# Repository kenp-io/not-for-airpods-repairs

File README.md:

# The Not-for-AirPods Repairs Directory

The content of this repository is licensed under the [WTFPL License](http://www.wtfpl.net/). Please have a close look at the terms before using this material. I would really appreciate it if you do the right thing and at least provide a link to my [YouTube channel](https://www.youtube.com/c/exploringthesimulation), but it is not compulsory.

Nothing in this repository is part of Apple's Intellectual Property. Any resemblance to actual products or registered trademarks is entirely coincidental.

Want to contribute to the project? Make a pull request! Please note that only technical contributions will be merged (requests like typo fixing won't be).

Please don't hesitate to star the repo if you want to be updated on this project :)

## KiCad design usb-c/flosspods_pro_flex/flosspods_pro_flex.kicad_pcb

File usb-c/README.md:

# The Not-for-AirPods USB-C Mod

Folder *flosspods_1_2_flex* contains the KiCad project if you want to order the PCB yourself. It works on Gen. 1 and Gen. 2 (both wired-only and wireless versions!). You need to generate the Gerber files yourself. There is an extra file called *flosspods_1_2_flex-stiffener.jpg*. It shows where I've placed the stiffener for the connector. It's nice to have but not a requirement. You send that file to the board house along with your Gerber files. Here it was sent to PCBWay.

File *bracket_1_2.dxf* is the metallic bracket I've ordered to be laser cut. It was cut in 0.5mm stainless steel.

File *sourcing.png* is a hint to find the source for the chips. I don't want to post those links. If you're smart enough to replicate this project, you're smart enough to find what you're looking for with this ;) If you can't find those chips, just use the same outline but adapt the circuit to the chips you found. Then you can make a pull request. Seems like a lot of effort, but if you want to learn there is no better way.

## Improvements for the future:

- Move to a waterproof connector. This is very low priority as the 3D printed case from the liberation kit also needs to be waterproof...
- Improve for mid-scale manufacturing run?

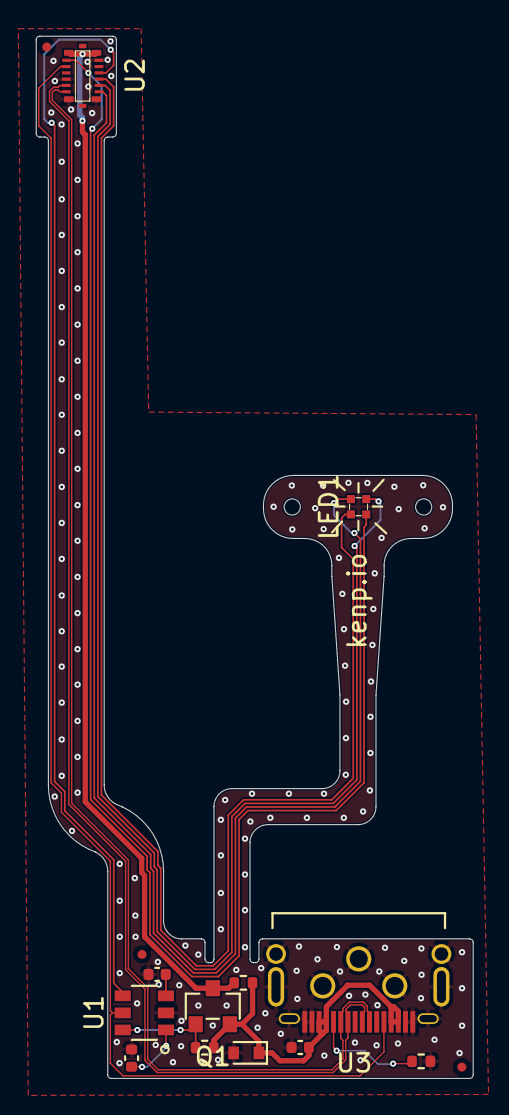
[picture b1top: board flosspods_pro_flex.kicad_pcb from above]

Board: 2 copper layers, 24.3 x 57.9 mm, 15 parts (0 on the bottom side), 15 nets.

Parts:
C1: 220n; C_0402_1005Metric
C2: 47n; C_0402_1005Metric
C3: 330n; C_0402_1005Metric
D1: D; D_SOD-523
FID1, FID2, FID3: Fiducial; Fiducial_0.5mm_Mask1mm
LED1: LED_LRTB_R48G
Q1: DMP2123L-7
R1: 100k; R_0402_1005Metric
R2: 120; R_0402_1005Metric
R8: 5.1k; R_0402_1005Metric
U1: C9419
U2: flosspods_pro_LightningMainBoard
U3: USBC_GT-USB-7022X

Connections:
/CC2: R8.2, U3.12 (CC2(B5))
/PMOS_D: Q1.2 (D), R2.1, U2.8 (PWR), U2.9 (PWR)
B: LED1.4 (W), U2.3 (LED1)
CC: U1.5 (CC), U2.11 (CC), U3.5 (CC1(A5))
D+: U2.15 (D+), U3.7 (D+(A6)), U3.11 (D+(B6))
D-: U2.14 (D-), U3.8 (D-(A7)), U3.10 (D-(B7))
G: LED1.3 (G), U2.2 (LED2)
GND: C1.1, C2.2, C3.2, D1.2 (A), R8.1, U1.2 (GND), U2.1 (GND), U2.7 (DGND), U2.13 (GND), U2.16 (GND), U3.1 (GND(A1)), U3.2 (GND(B12)), U3.15 (GND(A12)), U3.16 (GND(B1)), U3.S1 (SHIELD), U3.S2 (SHIELD), U3.S3 (SHIELD), U3.S4 (SHIELD), U3.S5 (SHIELD), U3.S6 (SHIELD), U3.S7 (SHIELD), U3.S8 (SHIELD), U3.S9 (SHIELD)
LED+: LED1.1 (LED+), U2.10 (LED4)
unnamed: C1.2, U1.1 (CC_CAP)
unnamed: C2.1, U1.3 (VCC)
unnamed: Q1.1 (G), R1.1, U1.6 (OUT1)
unnamed: U1.4 (AID), U2.5 (ID)
PMOS_S: C3.1, D1.1 (K), Q1.3 (S), R1.2, R2.2, U3.3 (VBUS(A4)), U3.4 (VBUS(B9)), U3.13 (VBUS(A9)), U3.14 (VBUS(B4))
R: LED1.2 (R), U2.4 (LED3)

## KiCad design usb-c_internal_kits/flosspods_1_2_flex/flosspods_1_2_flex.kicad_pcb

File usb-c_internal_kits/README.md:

# The Not-for-AirPods USB-C Mod

Folder *flosspods_1_2_flex* contains the KiCad project if you want to order the PCB yourself. It works on Gen. 1 and Gen. 2 (both wired-only and wireless versions!). You need to generate the Gerber files yourself. There is an extra file called *flosspods_1_2_flex-stiffener.jpg*. It shows where I've placed the stiffener for the connector. It's nice to have but not a requirement. You send that file to the board house along with your Gerber files. Here it was sent to PCBWay.

File *bracket_1_2.dxf* is the metallic bracket I've ordered to be laser cut. It was cut in 0.5mm stainless steel.

File *sourcing.png* is a hint to find the source for the chips. I don't want to post those links. If you're smart enough to replicate this project, you're smart enough to find what you're looking for with this ;) If you can't find those chips, just use the same outline but adapt the circuit to the chips you found. Then you can make a pull request. Seems like a lot of effort, but if you want to learn there is no better way.

---

Folder *flosspods_pro_flex* contains the KiCad project if you want to order the PCB yourself. It works on model Pro Gen. 1 (M4g$af3 and non-M4g$af3). You need to generate the Gerber files yourself. There is an extra file called *flosspods_pro_flex-stiffener.jpg*. It shows where I've placed the stiffener for the connector. It's nice to have but not a requirement. You send that file to the board house along with your Gerber files. Here it was sent to PCBWay.

File *bracket_pro.dxf* is the metallic bracket I've ordered to be laser cut. It was cut in 0.5mm stainless steel.

## Improvements for the future:

- Move to a waterproof connector. This is very low priority as the 3D printed case from the liberation kit also needs to be waterproof... (done for pro!)
- Improve for mid-scale manufacturing run? (done for pro!)

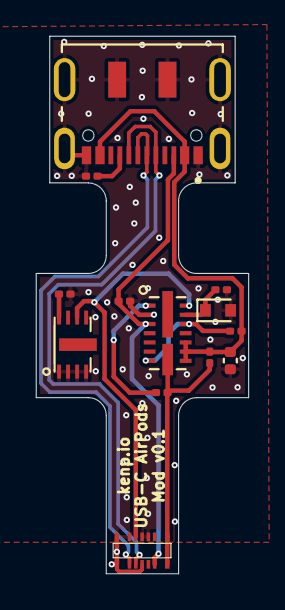
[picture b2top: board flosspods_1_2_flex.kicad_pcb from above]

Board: 2 copper layers, 11.8 x 29.9 mm, 13 parts (0 on the bottom side), 12 nets.

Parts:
C1: 1 uF; C_0201_0603Metric
C2: 10 nF; C_0201_0603Metric
C3: 330 nF; C_0402_1005Metric
D1: D; D_SOD-523
R1: 150; R_0201_0603Metric
R2: 100k; R_0201_0603Metric
R3: 1k; R_0201_0603Metric
R4, R5: 5.1k; R_0201_0603Metric
U1: AS3616Afake
U2: flosspods_1_2_LightningMainBoard
U3: PD006
U4: JAE_DX07S016JA1R1500

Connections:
/PWR: R1.1, R3.1, U1.F2, U2.1 (VCC), U2.14 (VCC)
CC: R4.1, U1.3, U2.13 (CC), U4.3 (CC1(A5))
D+: U2.9 (D+), U4.6 (D+(A6)), U4.7 (D+(B6))
D-: U2.10 (D-), U4.5 (D-(B7)), U4.8 (D-(A7))
GND: C1.1, C2.2, C3.1, D1.2 (A), R4.2, R5.1, U1.2, U2.3 (GND), U2.4 (GND), U2.6 (NC), U2.7 (GND), U2.8 (GND), U2.11 (GND), U3.1, U3.2, U3.3, U3.4, U3.5, U4.1 (GND(A1/B12)), U4.12 (GND(A12/B1)), U4.S1 (SHIELD), U4.S2 (SHIELD), U4.S3 (SHIELD), U4.S4 (SHIELD), U4.S5 (SHIELD), U4.S6 (SHIELD)
unnamed: C1.2, D1.1 (K), U1.13
unnamed: C2.1, U3.8
unnamed: R5.2, U4.9 (CC2(B5))
unnamed: R2.1, U1.7, U1.12
unnamed: R3.2, U1.1
unnamed: U1.14, U2.5 (ID), U3.6
VCC: C3.2, R1.2, R2.2, U1.8, U1.9, U1.10, U4.2 (VBUS(A4/B9)), U4.11 (VBUS(B4/B9))

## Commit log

2022-07-15 initial push
2022-07-15 picture fix
2022-07-15 picture fix 2
2022-07-15 rename pic
2022-07-15 fix text
2022-07-15 extra info
2022-07-20 video link
2023-02-08 added Pro model
2023-09-28 v2 3D parts
2024-10-02 folder cleanup
2024-10-02 ini protection cases
2024-10-15 max microphone holder
2025-04-19 max v7 added
